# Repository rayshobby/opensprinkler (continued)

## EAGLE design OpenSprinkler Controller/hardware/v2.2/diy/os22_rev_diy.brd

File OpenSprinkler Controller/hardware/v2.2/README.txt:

OpenSprinkler v2.2 (2nd generation)
Changes from 2.1

- Added CH340G USB-serial converter
- ATmega644 now running at 16MHz and preloaded with optiboot bootloader

DIY v2.2_rev and SMT v2.2

- Changed to use MC34063 switching regulator (previously LM2596)
- Added Microchip 24AA02E48 hardware MAC chip

Schematics and Board design files require EagleCAD v6.0 or above.

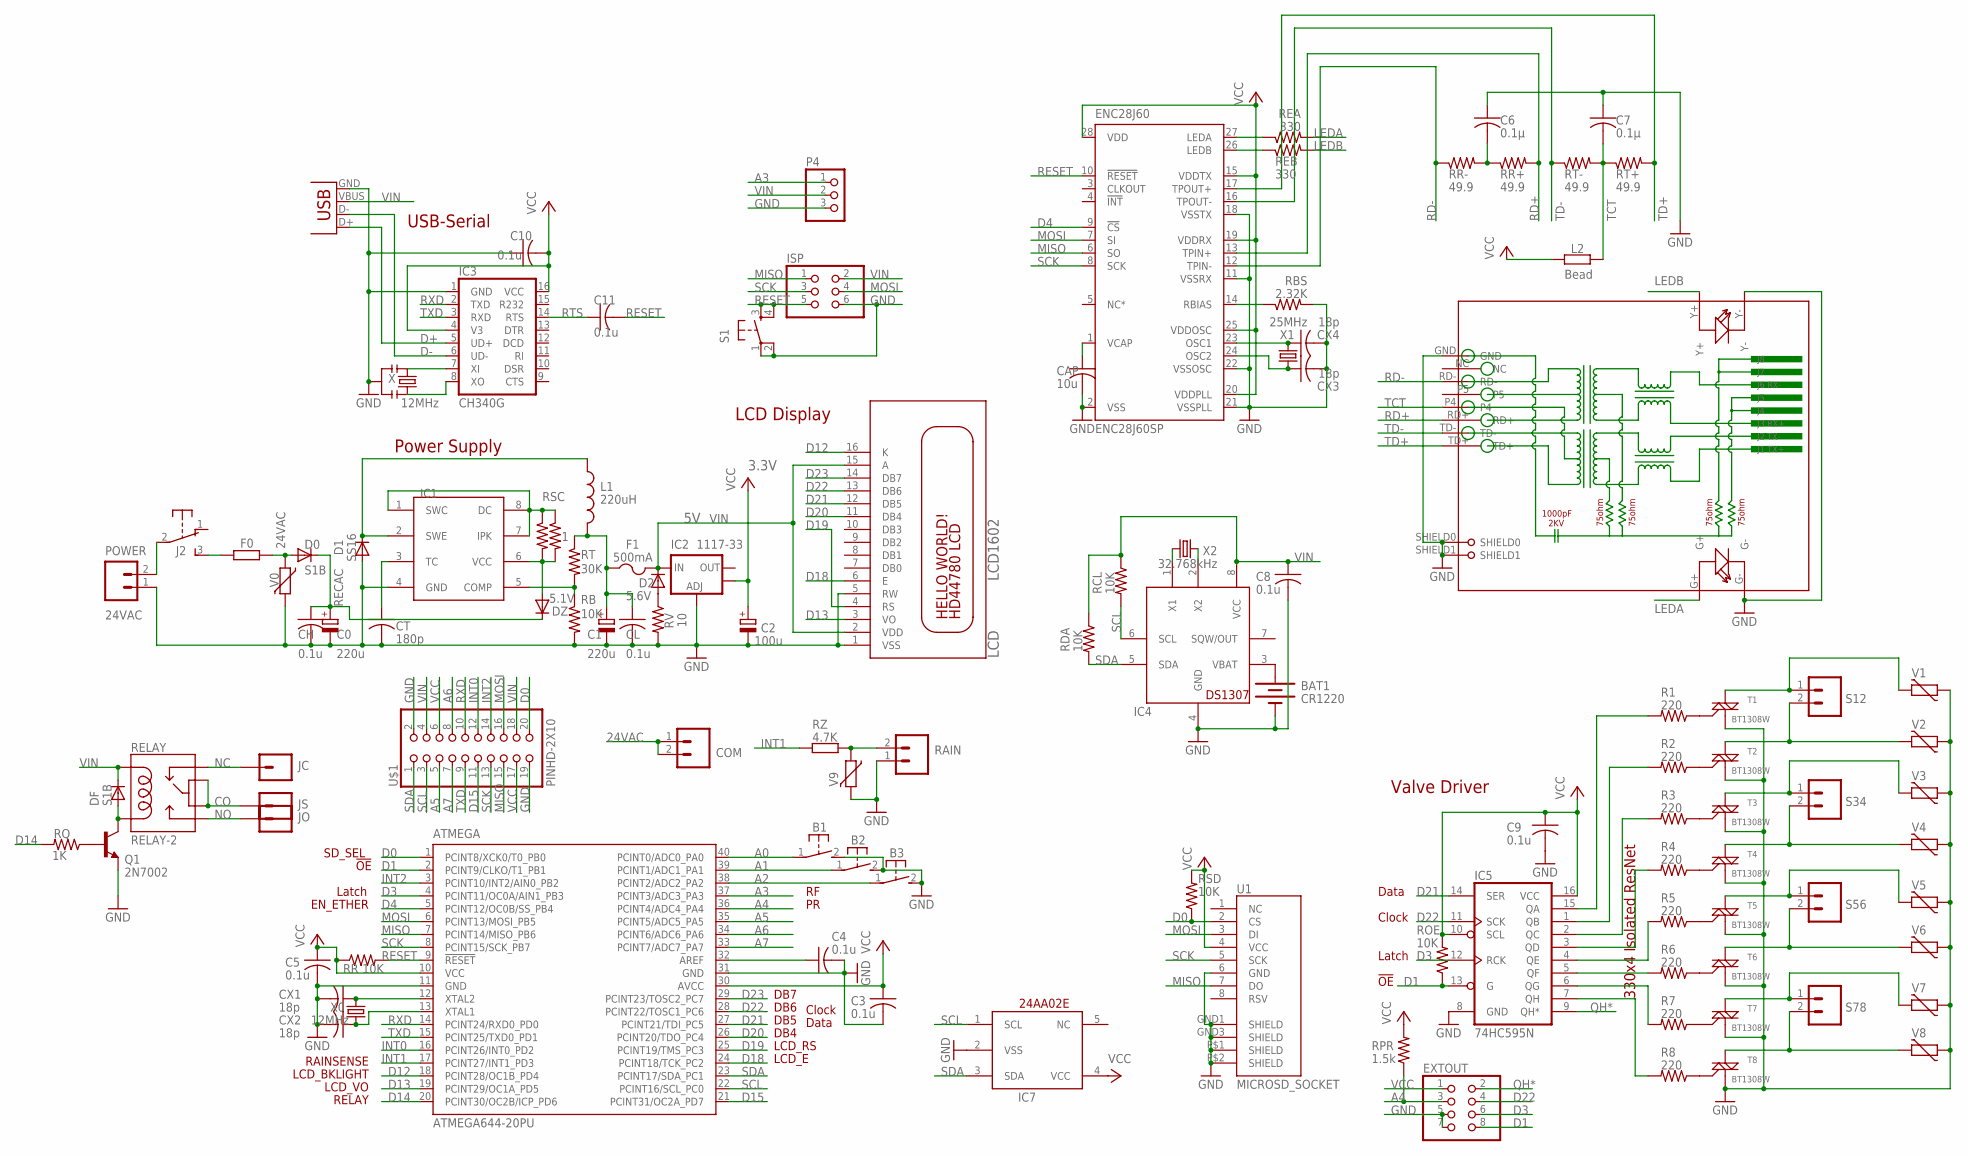
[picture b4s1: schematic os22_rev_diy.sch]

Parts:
ATMEGA: ATMEGA644-20PU; DIL40
B1, B2, B3: 31-XX; B3F-31XX
BAT1: CR1220; BATTCON_12MM_SMT
C0, C1: 220u; E3,5-8
C2: 100u; E2-5
C3, C4, C5, C8, C9, C10, C11: 0.1u; C0603K
C6, C7: 0.1µ; C0603K
CAP: 10u; C0805K
CH: 0.1u; C0603K
CL: 0.1u; C0603K
COM: M025MM-X; SCREWTERMINAL-5MM-2-X
CT: 180p; C0603K
CX1, CX2, CX3, CX4: 18p; C0603K
D0: S1B; DO-214AC
D1: SS16; DO-214AC
D2: 5.6V; MINIMELF
DF: S1B; DO-214AC
DZ: 5.1V; MELF-MLL41
ENC28J60: ENC28J60SP; DIL28-3
EXTOUT: PINHD-2X4; 2X04
F0: R-EU_0411/3V; 0411V
F1: 500mA; 1812
IC1: 34063; SO08
IC2: 1117-33; SOT223
IC3: CH340G; SO16
IC4: DS1307; SO08
IC5: 74HC595N; SO16
IC7: 24AA02E; SOT23-5L
ISP: PINHD-2X3; 2X03
J2: EG1206
JC: M01PTH; 1X01
JO: M01PTH; 1X01
JS: M01PTH; 1X01
L1: 220uH; 0204/5
L2: Bead; R0805
LCD: LCD1602; LCD1602A
P4: PINHD-1X3; 1X03
POWER: 24VAC; SCREWTERMINAL-4MM-2-X
Q1: 2N7002; SOT23-3
R1, R2, R3, R4, R5, R6, R7, R8: 220; R0603
RAIN: M025MM-X; SCREWTERMINAL-5MM-2-X
RB: 10K; R0805
RBS: 2.32K; R0805
RCL: 10K; R0603
RDA: 10K; R0603
REA: 330; R0603
REB: 330; R0603
RELAY: RELAY-2; RELAY-HK4100F
RJ45: HR911105A
ROE: 10K; R0603
RPR: 1.5k; R0603
RQ: 1K; R0603
RR: 10K; R0603
RR+: 49.9; R0805
RR-: 49.9; R0805
RSC, RSC1: 1; R0805
RSD: 10K; R0603
RT: 30K; R0805
RT+: 49.9; R0805
RT-: 49.9; R0805
RV: 10; R0805
RZ: 4.7K; R0805
S1: TAC_SWITCHPTH; TACTILE-PTH
S12, S34, S56, S78: M025MM-X; SCREWTERMINAL-5MM-2-X
T1, T2, T3, T4, T5, T6, T7, T8: BT1308W; TO-92
U1: MICROSD_SOCKET; MICRO-SD-SOCKET-TAOBAO
U$1: PINHD-2X10; 2X10-CLEANBIG
USB: USBPTH; USB-B-PTH
V0, V1, V2, V3, V4, V5, V6, V7, V8, V9: MOV; R-5
X: 12MHz; RESONATOR-SMD
X0: 12MHz; HC49U-V
X1: 25MHz; HC49U-V
X2: 32.768kHz; TC38H

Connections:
24VAC: COM.1, COM.2, D0.A, F0.2, V0.1
A0: ATMEGA.40 (PCINT0/ADC0_PA0), B1.1
A1: ATMEGA.39 (PCINT1/ADC1_PA1), B2.1
A2: ATMEGA.38 (PCINT2/ADC2_PA2), B3.1
A3: ATMEGA.37 (PCINT3/ADC3_PA3), P4.1
A4: ATMEGA.36 (PCINT4/ADC4_PA4), EXTOUT.3, RPR.1
A5: ATMEGA.35 (PCINT5/ADC5_PA5), U$1.5
A6: ATMEGA.34 (PCINT6/ADC6_PA6), U$1.8
A7: ATMEGA.33 (PCINT7/ADC7_PA7), U$1.7
AREF: ATMEGA.32 (AREF), C4.1
CO: JS.1, RELAY.5, RELAY.6
D0: ATMEGA.1 (PCINT8/XCK0/T0_PB0), RSD.1, U1.2 (CS), U$1.20
D1: ATMEGA.2 (PCINT9/CLKO/T1_PB1), EXTOUT.8, IC5.13 (G), ROE.1
D3: ATMEGA.4 (PCINT11/OC0A/AIN1_PB3), EXTOUT.6, IC5.12 (RCK)
D4: ATMEGA.5 (PCINT12/OC0B/SS_PB4), ENC28J60.9 (!CS)
D12: ATMEGA.18 (PCINT28/OC1B_PD4), LCD.16 (K)
D13: ATMEGA.19 (PCINT29/OC1A_PD5), LCD.3 (VO)
D14: ATMEGA.20 (PCINT30/OC2B/ICP_PD6), RQ.2
D15: ATMEGA.21 (PCINT31/OC2A_PD7), U$1.11
D18: ATMEGA.24 (PCINT18/TCK_PC2), LCD.6 (E)
D19: ATMEGA.25 (PCINT19/TMS_PC3), LCD.4 (RS)
D20: ATMEGA.26 (PCINT20/TDO_PC4), LCD.11 (DB4)
D21: ATMEGA.27 (PCINT21/TDI_PC5), IC5.14 (SER), LCD.12 (DB5)
D22: ATMEGA.28 (PCINT22/TOSC1_PC6), EXTOUT.4, IC5.11 (SCK), LCD.13 (DB6)
D23: ATMEGA.29 (PCINT23/TOSC2_PC7), LCD.14 (DB7)
D+: IC3.5 (UD+), USB.D+
D-: IC3.6 (UD-), USB.D-
GND: ATMEGA.11 (GND), ATMEGA.31 (GND), B1.2 (S), B2.2 (S), B3.2 (S), BAT1.P$1 (-), C0.-, C1.-, C2.-, C3.2, C4.2, C5.2, C6.1, C7.1, C8.2, C9.2, C10.1, CAP.2, CH.2, CL.2, CT.2, CX1.2, CX2.2, CX3.2, CX4.2, D1.A, ENC28J60.2 (VSS), ENC28J60.11 (VSSRX), ENC28J60.18 (VSSTX), ENC28J60.21 (VSSPLL), ENC28J60.22 (VSSOSC), EXTOUT.5, EXTOUT.7, IC1.4 (GND), IC2.1 (ADJ), IC3.1 (GND), IC4.4 (GND), IC5.8 (GND), IC7.2 (VSS), ISP.6, LCD.1 (VSS), LCD.5 (RW), P4.3, POWER.1, Q1.2 (E), RAIN.1, RB.2, RBS.2, RJ45.G-, RJ45.GND, RJ45.SHIELD0, RJ45.SHIELD1, RJ45.Y-, RV.2, S1.1, S1.2, T1.1 (M1), T2.1 (M1), T3.1 (M1), T4.1 (M1), T5.1 (M1), T6.1 (M1), T7.1 (M1), T8.1 (M1), U1.6 (GND), U1.GND1 (SHIELD), U1.GND3 (SHIELD), U1.P$1 (SHIELD), U1.P$2 (SHIELD), U$1.2, U$1.19, USB.GND, V0.2, V1.1, V2.1, V3.1, V4.1, V5.1, V6.1, V7.1, V8.1, V9.2, X.2
INT0: ATMEGA.16 (PCINT26/INT0_PD2), U$1.12
INT1: ATMEGA.17 (PCINT27/INT1_PD3), RZ.2
INT2: ATMEGA.3 (PCINT10/INT2/AIN0_PB2), U$1.14
LEDA: REA.2, RJ45.G+
LEDB: REB.2, RJ45.Y+
MISO: ATMEGA.7 (PCINT14/MISO_PB6), ENC28J60.6 (SO), ISP.1, U1.7 (DO), U$1.15
MOSI: ATMEGA.6 (PCINT13/MOSI_PB5), ENC28J60.7 (SI), ISP.4, U1.3 (DI), U$1.16
unnamed: IC4.2 (X2), X2.2
unnamed: IC4.1 (X1), X2.1
unnamed: R1.1, T1.2 (G)
unnamed: IC5.5 (QF), R6.2
unnamed: IC5.6 (QG), R7.2
unnamed: J2.2, POWER.2
unnamed: IC5.7 (QH), R8.2
unnamed: BAT1.P$2 (+), IC4.3 (VBAT)
unnamed: D1.C, IC1.2 (SWE), L1.1
unnamed: IC5.4 (QE), R5.2
unnamed: IC5.3 (QD), R4.2
unnamed: IC5.2 (QC), R3.2
unnamed: IC5.1 (QB), R2.2
unnamed: IC5.15 (QA), R1.2
unnamed: R2.1, T2.2 (G)
unnamed: S12.1, T1.3 (M2), V1.2
unnamed: S12.2, T2.3 (M2), V2.2
unnamed: S34.1, T3.3 (M2), V3.2
unnamed: ENC28J60.14 (RBIAS), RBS.1
unnamed: S34.2, T4.3 (M2), V4.2
unnamed: R3.1, T3.2 (G)
unnamed: S56.1, T5.3 (M2), V5.2
unnamed: S56.2, T6.3 (M2), V6.2
unnamed: S78.1, T7.3 (M2), V7.2
unnamed: S78.2, T8.3 (M2), V8.2
unnamed: R4.1, T4.2 (G)
unnamed: R5.1, T5.2 (G)
unnamed: R6.1, T6.2 (G)
unnamed: R7.1, T7.2 (G)
unnamed: RAIN.2, RZ.1, V9.1
unnamed: F0.1, J2.3 (S)
unnamed: CAP.1, ENC28J60.1 (VCAP)
unnamed: ENC28J60.27 (LEDA), REA.1
unnamed: DF.A, Q1.3 (C), RELAY.9
unnamed: ENC28J60.26 (LEDB), REB.1
unnamed: DZ.A, IC1.6 (VCC), RSC.2, RSC1.2
unnamed: D2.A, RV.1
unnamed: Q1.1 (B), RQ.1
unnamed: CX3.1, ENC28J60.24 (OSC2), X1.2
unnamed: CX4.1, ENC28J60.23 (OSC1), X1.1
unnamed: R8.1, T8.2 (G)
unnamed: IC3.7 (XI), X.1
unnamed: IC1.1 (SWC), IC1.7 (IPK), IC1.8 (DC), RSC.1, RSC1.1
unnamed: ATMEGA.12 (XTAL2), CX1.1, X0.2
unnamed: ATMEGA.13 (XTAL1), CX2.1, X0.1
unnamed: IC3.8 (XO), X.3
unnamed: CT.1, IC1.3 (TC)
unnamed: C6.2, RR+.1, RR-.2
unnamed: IC1.5 (COMP), RB.1, RT.2
NC: JC.1, RELAY.1
NO: JO.1, RELAY.10
QH*: EXTOUT.2, IC5.9 (QH*)
RD+: ENC28J60.13 (TPIN+), RJ45.RD+, RR+.2
RD-: ENC28J60.12 (TPIN-), RJ45.RD-, RR-.1
RECAC: C0.+, CH.1, D0.C, DZ.C
RESET: ATMEGA.9 (!RESET), C11.2, ENC28J60.10 (!RESET), ISP.5, RR.2, S1.3, S1.4
RTS: C11.1, IC3.14 (RTS)
RXD: ATMEGA.14 (PCINT24/RXD0_PD0), IC3.2 (TXD), U$1.10
SCK: ATMEGA.8 (PCINT15/SCK_PB7), ENC28J60.8 (SCK), ISP.3, U1.5 (SCK), U$1.13
SCL: ATMEGA.22 (PCINT16/SCL_PC0), IC4.6 (SCL), IC7.1 (SCL), RCL.2, U$1.3
SDA: ATMEGA.23 (PCINT17/SDA_PC1), IC4.5 (SDA), IC7.3 (SDA), RDA.2, U$1.1
TCT: C7.2, L2.1, RJ45.P4, RT+.1, RT-.2
TD+: ENC28J60.17 (TPOUT+), RJ45.TD+, RT+.2
TD-: ENC28J60.16 (TPOUT-), RJ45.TD-, RT-.1
TXD: ATMEGA.15 (PCINT25/TXD0_PD1), IC3.3 (RXD), U$1.9
VCC: ATMEGA.10 (VCC), ATMEGA.30 (AVCC), C2.+, C3.1, C5.1, C9.1, C10.2, ENC28J60.15 (VDDTX), ENC28J60.19 (VDDRX), ENC28J60.20 (VDDPLL), ENC28J60.25 (VDDOSC), ENC28J60.28 (VDD), EXTOUT.1, IC2.4 (OUT), IC3.4 (V3), IC3.16 (VCC), IC5.10 (SCL), IC5.16 (VCC), IC7.4 (VCC), L2.2, ROE.2, RPR.2, RR.1, RSD.2, U1.4 (VCC), U$1.6, U$1.17
VIN: C8.1, D2.C, DF.C, F1.2, IC2.3 (IN), IC4.8 (VCC), ISP.2, LCD.2 (VDD), LCD.15 (A), P4.2, RCL.1, RDA.1, RELAY.2, U$1.4, U$1.18, USB.VBUS
VIN1: C1.+, CL.1, F1.1, L1.2, RT.1

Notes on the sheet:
Valve Driver
Data
Clock
Latch
DB4
330x4 Isolated ResNet
LCD Display
EN_ETHER
3.3V
DB7
LCD_E
LCD_RS
DB6
DB5
!OE
RAINSENSE
LCD_BKLIGHT
LCD_VO
SD_SEL
RELAY
USB-Serial
Power Supply

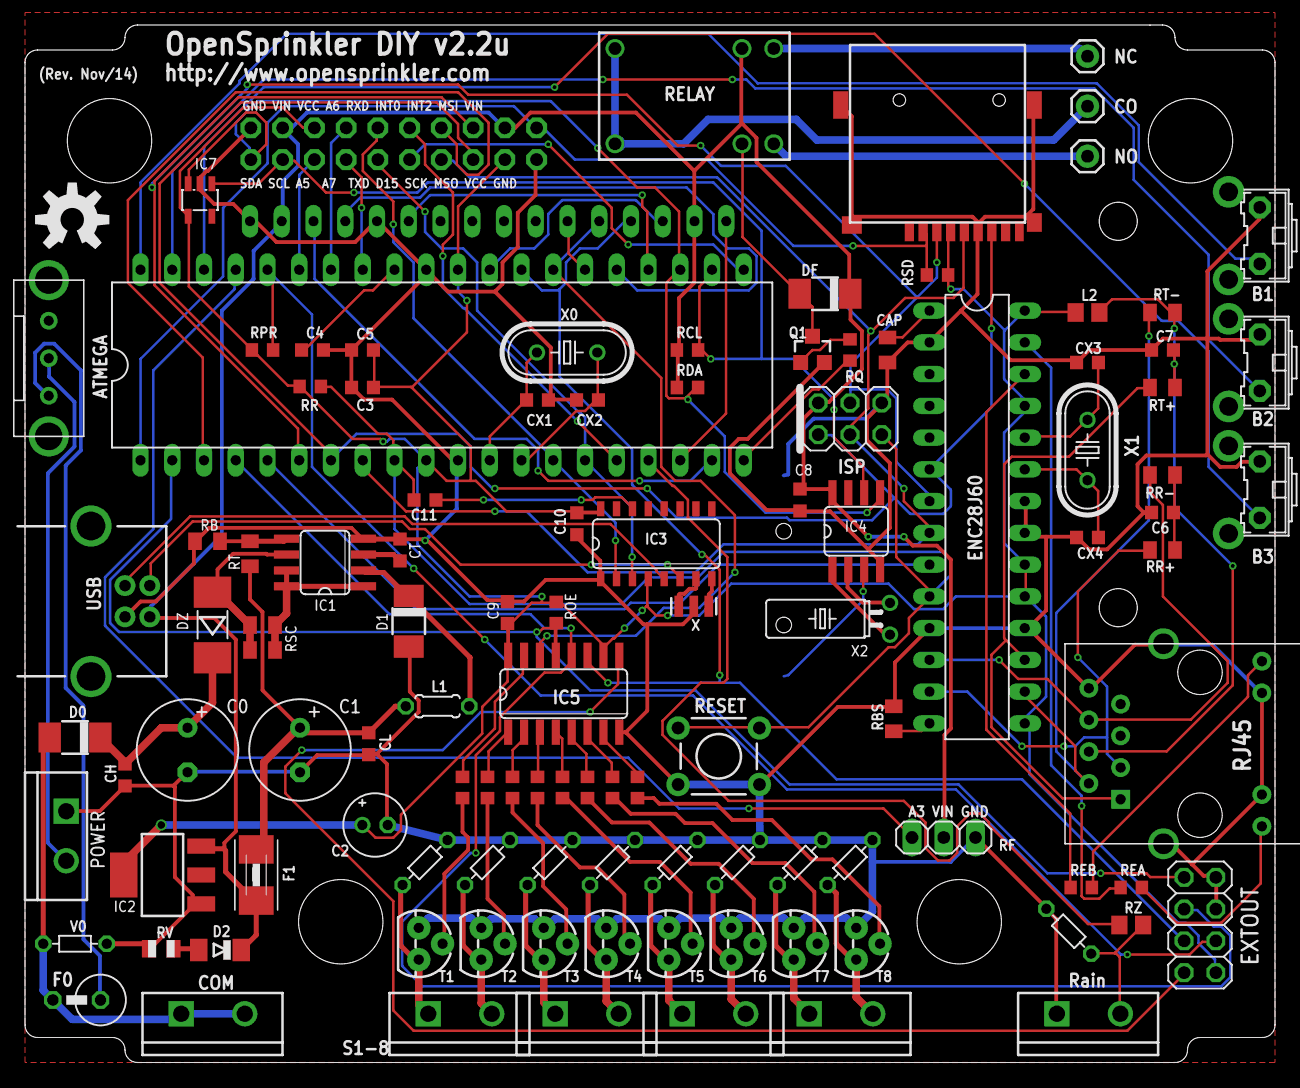
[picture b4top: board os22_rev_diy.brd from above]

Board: 2 copper layers, 100.0 x 83.0 mm, 113 parts (1 on the bottom side), 103 nets.

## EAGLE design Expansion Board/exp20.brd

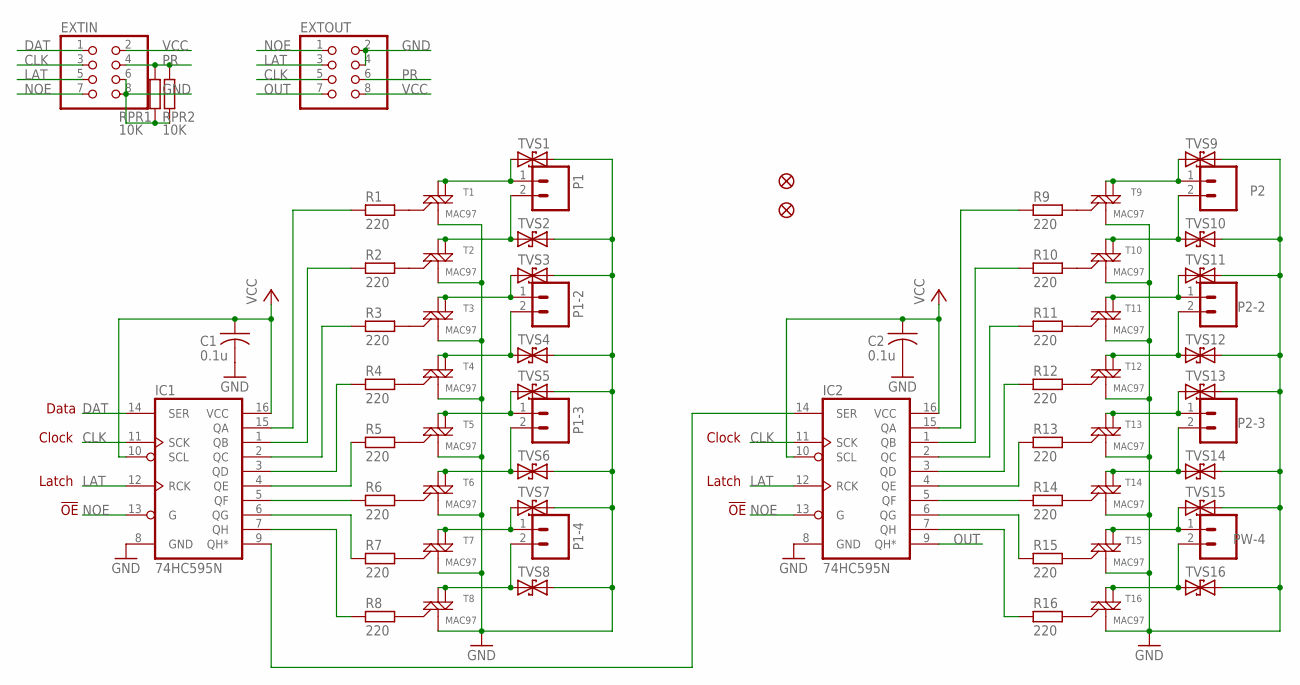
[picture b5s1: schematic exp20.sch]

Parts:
C1, C2: 0.1u; C0805K
EXTIN: PINHD-2X4/90; 2X04/90
EXTOUT: PINHD-2X4/90; 2X04/90
IC1, IC2: 74HC595N; SO16
JP1, JP2: FIDUCIAL1X2; FIDUCIAL-1X2
P1, P1-2, P1-3, P1-4, P2, P2-2, P2-3: M025MM-X; SCREWTERMINAL-5MM-2-X
PW-4: M025MM-X; SCREWTERMINAL-5MM-2-X
R1, R2, R3, R4, R5, R6, R7, R8, R9, R10, R11, R12, R13, R14, R15, R16: 220; R0805
RPR1, RPR2: 10K; R0805
T1, T2, T3, T4, T5, T6, T7, T8, T9, T10, T11, T12, T13, T14, T15, T16: MAC97; SOT223
TVS1, TVS2, TVS3, TVS4, TVS5, TVS6, TVS7, TVS8, TVS9, TVS10, TVS11, TVS12, TVS13, TVS14, TVS15, TVS16: TVSSMB; SMB

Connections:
CLK: EXTIN.3, EXTOUT.5, IC1.11 (SCK), IC2.11 (SCK)
DAT: EXTIN.1, IC1.14 (SER)
GND: C1.2, C2.2, EXTIN.6, EXTIN.8, EXTOUT.2, EXTOUT.4, IC1.8 (GND), IC2.8 (GND), RPR1.1, RPR2.1, T1.1 (M1), T2.1 (M1), T3.1 (M1), T4.1 (M1), T5.1 (M1), T6.1 (M1), T7.1 (M1), T8.1 (M1), T9.1 (M1), T10.1 (M1), T11.1 (M1), T12.1 (M1), T13.1 (M1), T14.1 (M1), T15.1 (M1), T16.1 (M1), TVS1.C (2), TVS2.C (2), TVS3.C (2), TVS4.C (2), TVS5.C (2), TVS6.C (2), TVS7.C (2), TVS8.C (2), TVS9.C (2), TVS10.C (2), TVS11.C (2), TVS12.C (2), TVS13.C (2), TVS14.C (2), TVS15.C (2), TVS16.C (2)
LAT: EXTIN.5, EXTOUT.3, IC1.12 (RCK), IC2.12 (RCK)
unnamed: P1.1, T1.2 (M2), T1.4 (M2-4), TVS1.A (1)
unnamed: P1-2.1, T3.2 (M2), T3.4 (M2-4), TVS3.A (1)
unnamed: P1-3.1, T5.2 (M2), T5.4 (M2-4), TVS5.A (1)
unnamed: IC1.5 (QF), R6.2
unnamed: IC1.6 (QG), R7.2
unnamed: P1-4.1, T7.2 (M2), T7.4 (M2-4), TVS7.A (1)
unnamed: IC1.7 (QH), R8.2
unnamed: R1.1, T1.3 (G)
unnamed: R2.1, T2.3 (G)
unnamed: IC1.4 (QE), R5.2
unnamed: IC1.3 (QD), R4.2
unnamed: IC1.2 (QC), R3.2
unnamed: IC1.1 (QB), R2.2
unnamed: IC1.15 (QA), R1.2
unnamed: R3.1, T3.3 (G)
unnamed: R4.1, T4.3 (G)
unnamed: P1.2, T2.2 (M2), T2.4 (M2-4), TVS2.A (1)
unnamed: R5.1, T5.3 (G)
unnamed: R6.1, T6.3 (G)
unnamed: P1-2.2, T4.2 (M2), T4.4 (M2-4), TVS4.A (1)
unnamed: R7.1, T7.3 (G)
unnamed: R8.1, T8.3 (G)
unnamed: P1-3.2, T6.2 (M2), T6.4 (M2-4), TVS6.A (1)
unnamed: IC2.5 (QF), R14.2
unnamed: P1-4.2, T8.2 (M2), T8.4 (M2-4), TVS8.A (1)
unnamed: IC2.6 (QG), R15.2
unnamed: IC2.7 (QH), R16.2
unnamed: IC2.4 (QE), R13.2
unnamed: IC2.3 (QD), R12.2
unnamed: IC2.2 (QC), R11.2
unnamed: IC2.1 (QB), R10.2
unnamed: IC2.15 (QA), R9.2
unnamed: P2.2, T10.2 (M2), T10.4 (M2-4), TVS10.A (1)
unnamed: P2-2.2, T12.2 (M2), T12.4 (M2-4), TVS12.A (1)
unnamed: P2-3.2, T14.2 (M2), T14.4 (M2-4), TVS14.A (1)
unnamed: PW-4.2, T16.2 (M2), T16.4 (M2-4), TVS16.A (1)
unnamed: P2.1, T9.2 (M2), T9.4 (M2-4), TVS9.A (1)
unnamed: P2-2.1, T11.2 (M2), T11.4 (M2-4), TVS11.A (1)
unnamed: P2-3.1, T13.2 (M2), T13.4 (M2-4), TVS13.A (1)
unnamed: PW-4.1, T15.2 (M2), T15.4 (M2-4), TVS15.A (1)
unnamed: R9.1, T9.3 (G)
unnamed: R10.1, T10.3 (G)
unnamed: R11.1, T11.3 (G)
unnamed: R12.1, T12.3 (G)
unnamed: R13.1, T13.3 (G)
unnamed: R14.1, T14.3 (G)
unnamed: R15.1, T15.3 (G)
unnamed: R16.1, T16.3 (G)
unnamed: IC1.9 (QH*), IC2.14 (SER)
NOE: EXTIN.7, EXTOUT.1, IC1.13 (G), IC2.13 (G)
OUT: EXTOUT.7, IC2.9 (QH*)
PR: EXTIN.4, EXTOUT.6, RPR1.2, RPR2.2
VCC: C1.1, C2.1, EXTIN.2, EXTOUT.8, IC1.10 (SCL), IC1.16 (VCC), IC2.10 (SCL), IC2.16 (VCC)

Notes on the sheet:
Data
Clock
Latch
!OE

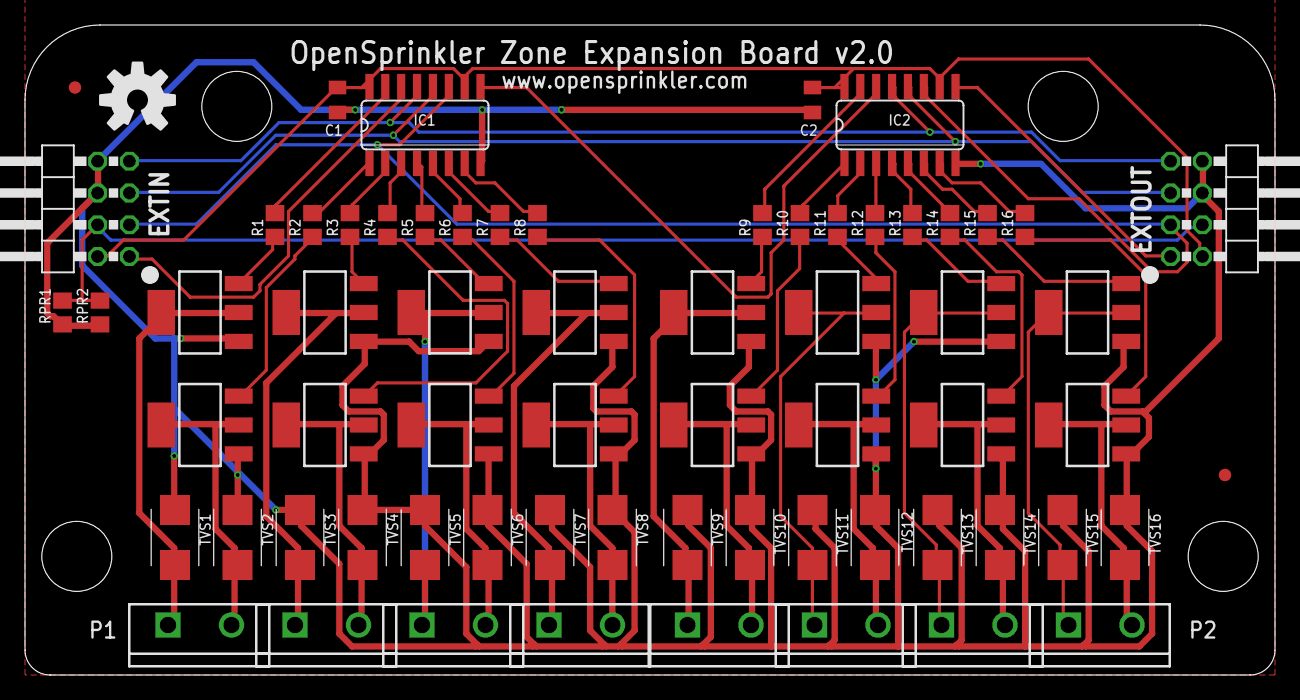
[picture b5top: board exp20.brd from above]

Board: 2 copper layers, 100.0 x 52.0 mm, 66 parts (0 on the bottom side), 57 nets.

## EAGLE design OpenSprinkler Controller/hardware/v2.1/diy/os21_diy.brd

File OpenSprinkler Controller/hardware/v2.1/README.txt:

OpenSprinkler v2.1 (2nd generation)
Changes from 2.0

- Removed ATtiny45 (used to serve as USBtinyISP programmer).
- ATmega644 now running at 12MHz and preloaded with USBasp bootloader.
- Added per-station TVS (smt version) / MOV (diy version).
- Added 120V/2A mini-relay (connected to pin D14.
- Added 2A fuse on the 24V AC line.
- 24V AC terminal block changed to orange colored 3.96mm spacing.

Schematics and Board design files require EagleCAD v6.0 or above.

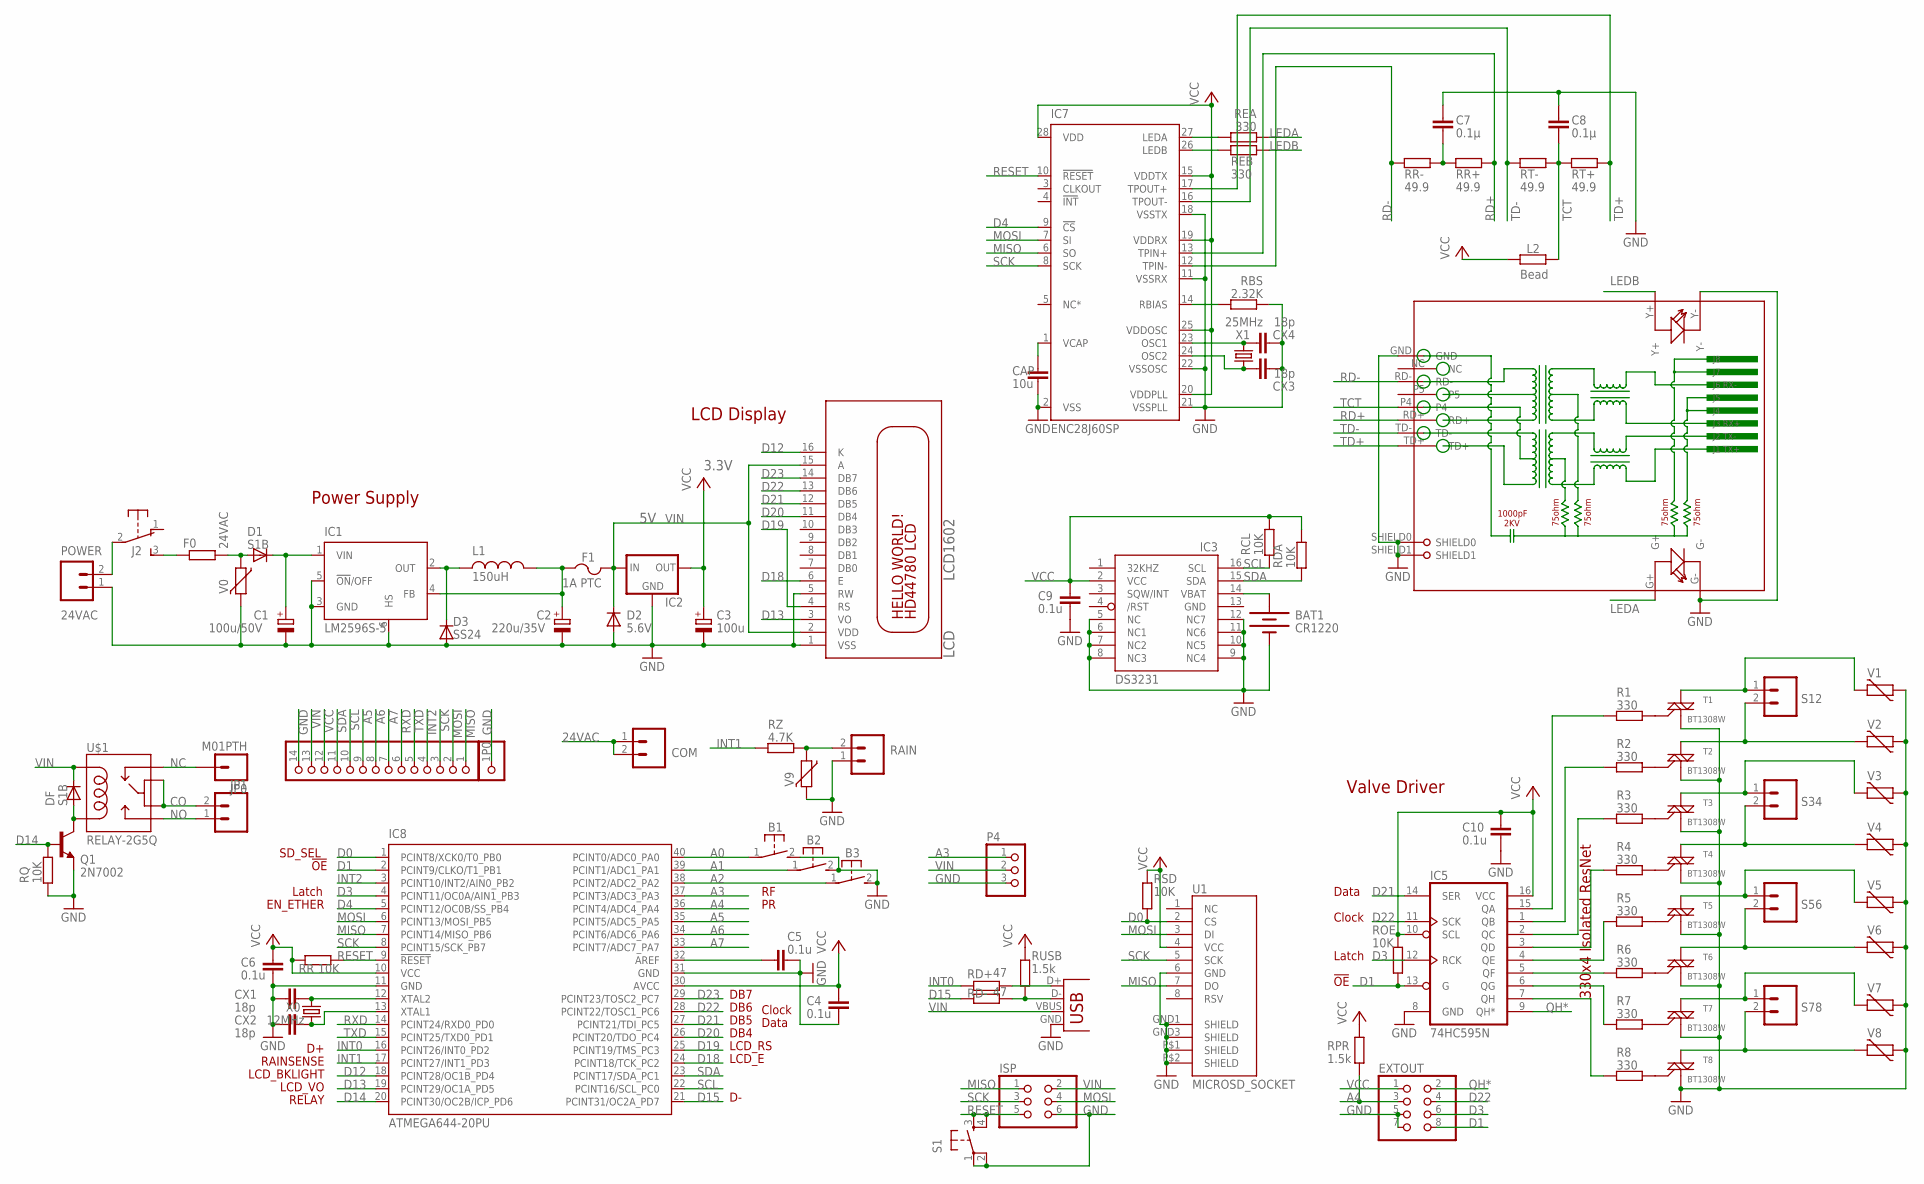
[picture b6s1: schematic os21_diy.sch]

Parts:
B1, B2, B3: 31-XX; B3F-31XX
BAT1: CR1220; BATTCON_12MM_SMT
C1: 100u/50V; E3,5-8
C2: 220u/35V; E3,5-8
C3: 100u; E2-5
C4, C5, C6, C9, C10: 0.1u; C0805
C7, C8: 0.1µ; C0805
CAP: 10u; C0805
COM: M025MM-X; SCREWTERMINAL-5MM-2-X
CX1, CX2, CX3, CX4: 18p; C0805
D1: S1B; DO-214AC
D2: 5.6V; MINIMELF
D3: SS24; DO-214AC
DF: S1B; DO-214AC
EXTOUT: PINHD-2X4; 2X04
F0: R-EU_0411/3V; 0411V
F1: 1A PTC; 1812
IC1: LM2596S-5; TO263-5
IC2: MCP1700SOT233; SOT23
IC3: DS3231/SO; SO16W
IC5: 74HC595N; SO16
IC7: ENC28J60SP; DIL28-3
IC8: ATMEGA644-20PU; DIL40
ISP: PINHD-2X3; 2X03
J2: EG1206
JP0: M01PTH; 1X01
JP1: M025MM-X; SCREWTERMINAL-5MM-2-X
L1: 150uH; CDRH125
L2: Bead; R0805
LCD: LCD1602; LCD1602A
P0: PINHD-1X14-CB; 1X14-CB
P1: PINHD-1X1CB; 1X01-CLEANBIG
P4: PINHD-1X3; 1X03
POWER: 24VAC; SCREWTERMINAL-4MM-2-X
Q1: 2N7002; SOT23-3
R1, R2, R3, R4, R5, R6, R7, R8: 330; R0805
RAIN: M025MM-X; SCREWTERMINAL-5MM-2-X
RBS: 2.32K; R0805
RCL: 10K; R0805
RD+: 47; R0805
RD-: 47; R0805
RDA: 10K; R0805
REA: 330; R0805
REB: 330; R0805
RJ45: HR911105A
ROE: 10K; R0805
RPR: 1.5k; R0805
RQ: 10K; R0805
RR: 10K; R0805
RR+: 49.9; R0805
RR-: 49.9; R0805
RSD: 10K; R0805
RT+: 49.9; R0805
RT-: 49.9; R0805
RUSB: 1.5k; R0805
RZ: 4.7K; R0805
S1: TAC_SWITCHSMD; TACTILE_SWITCH_SMD
S12, S34, S56, S78: M025MM-X; SCREWTERMINAL-5MM-2-X
T1, T2, T3, T4, T5, T6, T7, T8: BT1308W; TO-92
U1: MICROSD_SOCKET; MICRO-SD-SOCKET-TAOBAO
U$1: RELAY-2G5Q; RELAY-G5V
USB: USBPTH; USB-B-PTH
V0, V1, V2, V3, V4, V5, V6, V7, V8, V9: MOV; R-5
X0: 12MHz; HC49U-V
X1: 25MHz; HC49U-V

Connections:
24VAC: COM.1, COM.2, D1.A, F0.2, V0.1
A0: B1.1, IC8.40 (PCINT0/ADC0_PA0)
A1: B2.1, IC8.39 (PCINT1/ADC1_PA1)
A2: B3.1, IC8.38 (PCINT2/ADC2_PA2)
A3: IC8.37 (PCINT3/ADC3_PA3), P4.1
A4: EXTOUT.3, IC8.36 (PCINT4/ADC4_PA4), RPR.1
A5: IC8.35 (PCINT5/ADC5_PA5), P0.9
A6: IC8.34 (PCINT6/ADC6_PA6), P0.8
A7: IC8.33 (PCINT7/ADC7_PA7), P0.7
AREF: C5.1, IC8.32 (AREF)
CO: JP1.2, U$1.5, U$1.6
D0: IC8.1 (PCINT8/XCK0/T0_PB0), RSD.1, U1.2 (CS)
D1: EXTOUT.8, IC5.13 (G), IC8.2 (PCINT9/CLKO/T1_PB1), ROE.1
D3: EXTOUT.6, IC5.12 (RCK), IC8.4 (PCINT11/OC0A/AIN1_PB3)
D4: IC7.9 (!CS), IC8.5 (PCINT12/OC0B/SS_PB4)
D12: IC8.18 (PCINT28/OC1B_PD4), LCD.16 (K)
D13: IC8.19 (PCINT29/OC1A_PD5), LCD.3 (VO)
D14: IC8.20 (PCINT30/OC2B/ICP_PD6), Q1.1 (B), RQ.1
D15: IC8.21 (PCINT31/OC2A_PD7), RD-.1
D18: IC8.24 (PCINT18/TCK_PC2), LCD.6 (E)
D19: IC8.25 (PCINT19/TMS_PC3), LCD.4 (RS)
D20: IC8.26 (PCINT20/TDO_PC4), LCD.11 (DB4)
D21: IC5.14 (SER), IC8.27 (PCINT21/TDI_PC5), LCD.12 (DB5)
D22: EXTOUT.4, IC5.11 (SCK), IC8.28 (PCINT22/TOSC1_PC6), LCD.13 (DB6)
D23: IC8.29 (PCINT23/TOSC2_PC7), LCD.14 (DB7)
GND: B1.2 (S), B2.2 (S), B3.2 (S), BAT1.P$1 (-), C1.-, C2.-, C3.-, C4.2, C5.2, C6.2, C7.1, C8.1, C9.2, C10.2, CAP.2, CX1.2, CX2.2, CX3.2, CX4.2, D2.A, D3.A, EXTOUT.5, EXTOUT.7, IC1.3 (GND), IC1.5 (!ON!/OFF), IC1.6 (HS), IC2.1 (GND), IC3.5 (NC), IC3.6 (NC1), IC3.7 (NC2), IC3.8 (NC3), IC3.9 (NC4), IC3.10 (NC5), IC3.11 (NC6), IC3.12 (NC7), IC3.13 (GND), IC5.8 (GND), IC7.2 (VSS), IC7.11 (VSSRX), IC7.18 (VSSTX), IC7.21 (VSSPLL), IC7.22 (VSSOSC), IC8.11 (GND), IC8.31 (GND), ISP.6, LCD.1 (VSS), LCD.5 (RW), P0.14, P1.1, P4.3, POWER.1, Q1.2 (E), RAIN.1, RBS.2, RJ45.G-, RJ45.GND, RJ45.SHIELD0, RJ45.SHIELD1, RJ45.Y-, RQ.2, S1.1, S1.2, T1.1 (M1), T2.1 (M1), T3.1 (M1), T4.1 (M1), T5.1 (M1), T6.1 (M1), T7.1 (M1), T8.1 (M1), U1.6 (GND), U1.GND1 (SHIELD), U1.GND3 (SHIELD), U1.P$1 (SHIELD), U1.P$2 (SHIELD), USB.GND, V0.2, V1.1, V2.1, V3.1, V4.1, V5.1, V6.1, V7.1, V8.1, V9.2
INT0: IC8.16 (PCINT26/INT0_PD2), RD+.1
INT1: IC8.17 (PCINT27/INT1_PD3), RZ.2
INT2: IC8.3 (PCINT10/INT2/AIN0_PB2), P0.4
LEDA: REA.2, RJ45.G+
LEDB: REB.2, RJ45.Y+
MISO: IC7.6 (SO), IC8.7 (PCINT14/MISO_PB6), ISP.1, P0.1, U1.7 (DO)
MOSI: IC7.7 (SI), IC8.6 (PCINT13/MOSI_PB5), ISP.4, P0.2, U1.3 (DI)
unnamed: C1.+, D1.C, IC1.1 (VIN)
unnamed: C2.+, F1.1, IC1.4 (FB), L1.2
unnamed: R1.1, T1.2 (G)
unnamed: IC5.5 (QF), R6.2
unnamed: IC5.6 (QG), R7.2
unnamed: J2.2, POWER.2
unnamed: IC5.7 (QH), R8.2
unnamed: BAT1.P$2 (+), IC3.14 (VBAT)
unnamed: D3.C, IC1.2 (OUT), L1.1
unnamed: IC5.4 (QE), R5.2
unnamed: IC5.3 (QD), R4.2
unnamed: IC5.2 (QC), R3.2
unnamed: IC5.1 (QB), R2.2
unnamed: IC5.15 (QA), R1.2
unnamed: R2.1, T2.2 (G)
unnamed: S12.1, T1.3 (M2), V1.2
unnamed: S12.2, T2.3 (M2), V2.2
unnamed: S34.1, T3.3 (M2), V3.2
unnamed: IC7.14 (RBIAS), RBS.1
unnamed: S34.2, T4.3 (M2), V4.2
unnamed: R3.1, T3.2 (G)
unnamed: S56.1, T5.3 (M2), V5.2
unnamed: S56.2, T6.3 (M2), V6.2
unnamed: S78.1, T7.3 (M2), V7.2
unnamed: S78.2, T8.3 (M2), V8.2
unnamed: R4.1, T4.2 (G)
unnamed: R5.1, T5.2 (G)
unnamed: R6.1, T6.2 (G)
unnamed: R7.1, T7.2 (G)
unnamed: RAIN.2, RZ.1, V9.1
unnamed: F0.1, J2.3 (S)
unnamed: CAP.1, IC7.1 (VCAP)
unnamed: IC7.27 (LEDA), REA.1
unnamed: DF.A, Q1.3 (C), U$1.9
unnamed: IC7.26 (LEDB), REB.1
unnamed: RD+.2, USB.D+
unnamed: CX3.1, IC7.24 (OSC2), X1.2
unnamed: CX4.1, IC7.23 (OSC1), X1.1
unnamed: R8.1, T8.2 (G)
unnamed: RD-.2, RUSB.1, USB.D-
unnamed: CX1.1, IC8.12 (XTAL2), X0.2
unnamed: CX2.1, IC8.13 (XTAL1), X0.1
unnamed: C7.2, RR+.1, RR-.2
NC: JP0.1, U$1.1
NO: JP1.1, U$1.10
QH*: EXTOUT.2, IC5.9 (QH*)
RD+: IC7.13 (TPIN+), RJ45.RD+, RR+.2
RD-: IC7.12 (TPIN-), RJ45.RD-, RR-.1
RESET: IC7.10 (!RESET), IC8.9 (!RESET), ISP.5, RR.2, S1.3, S1.4
RXD: IC8.14 (PCINT24/RXD0_PD0), P0.6
SCK: IC7.8 (SCK), IC8.8 (PCINT15/SCK_PB7), ISP.3, P0.3, U1.5 (SCK)
SCL: IC3.16 (SCL), IC8.22 (PCINT16/SCL_PC0), P0.10, RCL.2
SDA: IC3.15 (SDA), IC8.23 (PCINT17/SDA_PC1), P0.11, RDA.2
TCT: C8.2, L2.1, RJ45.P4, RT+.1, RT-.2
TD+: IC7.17 (TPOUT+), RJ45.TD+, RT+.2
TD-: IC7.16 (TPOUT-), RJ45.TD-, RT-.1
TXD: IC8.15 (PCINT25/TXD0_PD1), P0.5
VCC: C3.+, C4.1, C6.1, C9.1, C10.1, EXTOUT.1, IC2.2 (OUT), IC3.2 (VCC), IC5.10 (SCL), IC5.16 (VCC), IC7.15 (VDDTX), IC7.19 (VDDRX), IC7.20 (VDDPLL), IC7.25 (VDDOSC), IC7.28 (VDD), IC8.10 (VCC), IC8.30 (AVCC), L2.2, P0.12, RCL.1, RDA.1, ROE.2, RPR.2, RR.1, RSD.2, RUSB.2, U1.4 (VCC)
VIN: D2.C, DF.C, F1.2, IC2.3 (IN), ISP.2, LCD.2 (VDD), LCD.15 (A), P0.13, P4.2, U$1.2, USB.VBUS

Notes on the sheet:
Power Supply
Valve Driver
Data
Clock
Latch
DB4
330x4 Isolated ResNet
LCD Display
EN_ETHER
3.3V
DB7
LCD_E
LCD_RS
DB6
DB5
!OE
RAINSENSE
LCD_BKLIGHT
LCD_VO
SD_SEL
RELAY

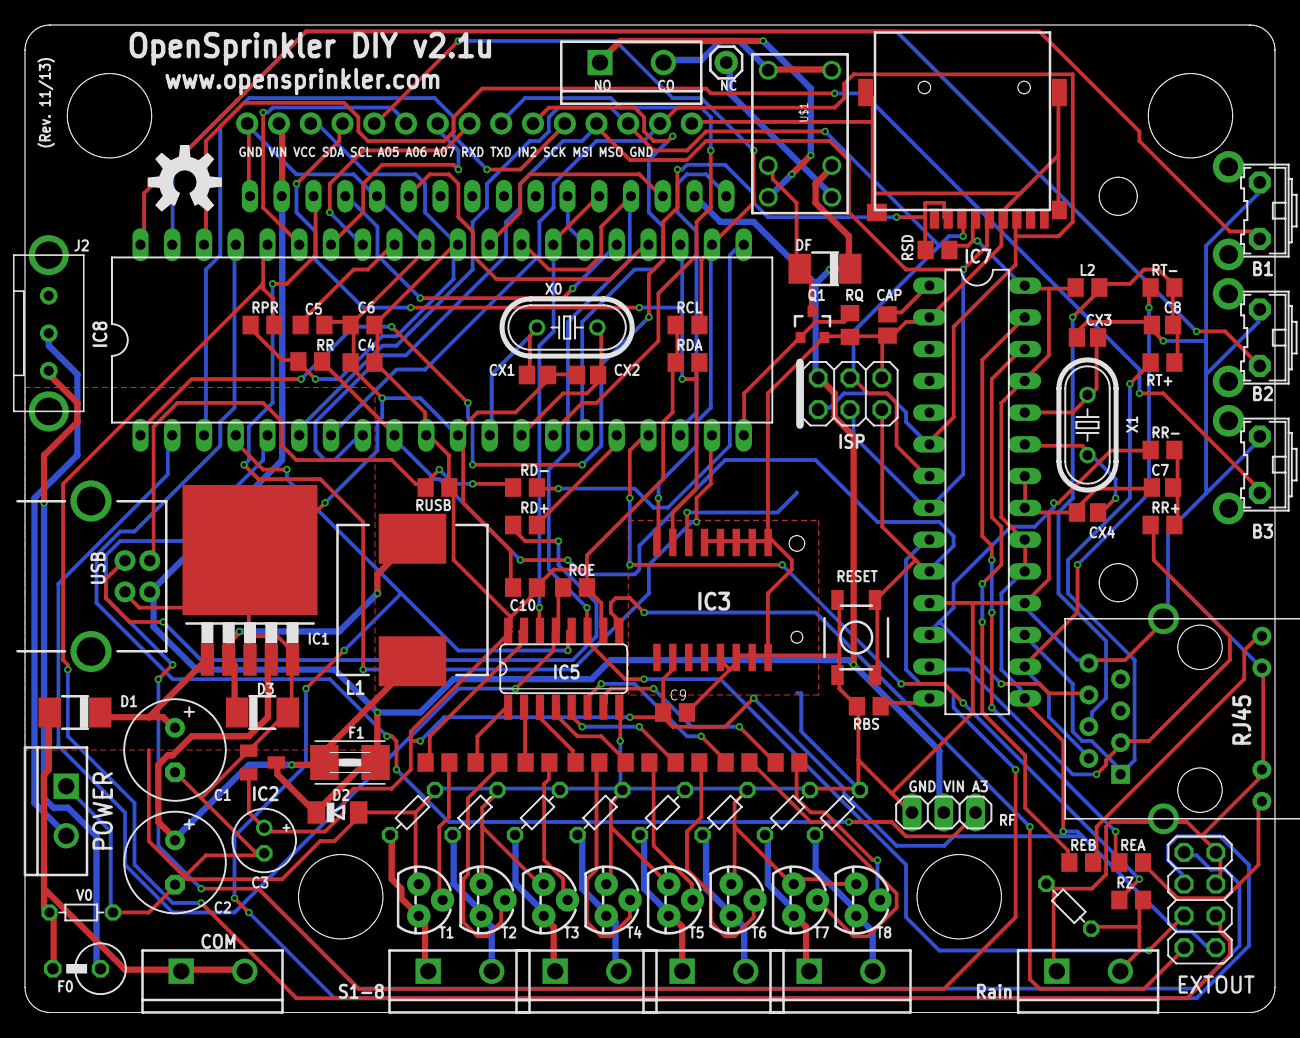
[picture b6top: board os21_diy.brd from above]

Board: 2 copper layers, 100.0 x 79.0 mm, 101 parts (1 on the bottom side), 92 nets.

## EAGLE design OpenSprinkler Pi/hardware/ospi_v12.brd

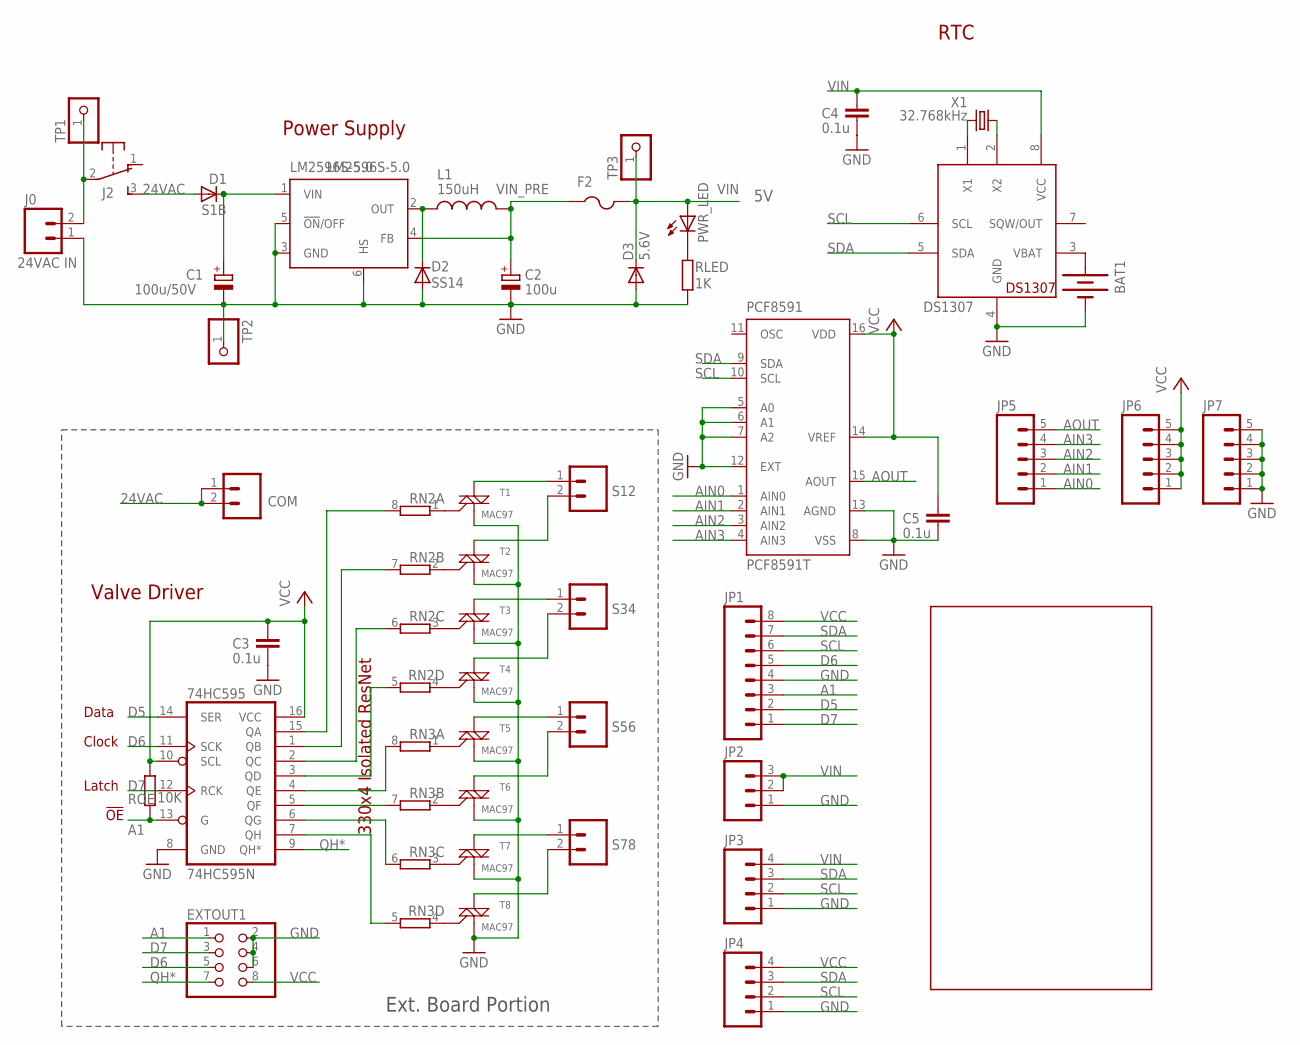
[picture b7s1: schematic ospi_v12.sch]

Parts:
74HC595: 74HC595N; SO16
BAT1: BATTERYBATTERY_12MM_SMT; BATTCON_12MM_SMT
C1: 100u/50V; PANASONIC_E
C2: 100u; PANASONIC_E
C3, C4, C5: 0.1u; C0805
COM: M025MM; SCREWTERMINAL-5MM-2
D1: S1B; DO-214AC
D2: SS14; DO-214AC
D3: 5.6V; MINIMELF
DS1307: DS1307; SO08
EXTOUT1: PINHD-2X4/90; 2X04/90
F2: PTCFUSE-1812; 1812
J0: 24VAC IN; SCREWTERMINAL-5MM-2
J2: EG1206
JP1: M08LOCK; 1X08_LOCK
JP2: M03LOCK; 1X03_LOCK
JP3, JP4: M04LOCK; 1X04_LOCK
JP5, JP6, JP7: M05LOCK; 1X05_LOCK
L1: 150uH; CDRH125
LM2596S-5.0: LM2596S-5.0; TO263-5
PCF8591: PCF8591T; SO16W
PWR_LED: LEDCHIPLED_0805; CHIPLED_0805
RLED: 1K; R0805
RN2, RN3: 4R-NEXB38V; EXB38V
ROE: 10K; R0805
S12, S34, S56, S78: M025MM; SCREWTERMINAL-5MM-2
T1, T2, T3, T4, T5, T6, T7, T8: MAC97; SOT223
TP1, TP2, TP3: PINHD-1X1CB; 1X01-CLEANBIG
U$2: OSPI
X1: 32.768kHz; MM20SS

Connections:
24VAC: COM.1, COM.2, D1.A, J2.3 (S)
A1: 74HC595.13 (G), EXTOUT1.1, JP1.3, ROE.1
AIN0: JP5.1, PCF8591.1 (AIN0)
AIN1: JP5.2, PCF8591.2 (AIN1)
AIN2: JP5.3, PCF8591.3 (AIN2)
AIN3: JP5.4, PCF8591.4 (AIN3)
AOUT: JP5.5, PCF8591.15 (AOUT)
D5: 74HC595.14 (SER), JP1.2
D6: 74HC595.11 (SCK), EXTOUT1.5, JP1.5
D7: 74HC595.12 (RCK), EXTOUT1.3, JP1.1
GND: 74HC595.8 (GND), BAT1.P$1 (-), C1.-, C2.-, C3.2, C4.2, C5.2, D2.A, D3.A, DS1307.4 (GND), EXTOUT1.2, EXTOUT1.4, EXTOUT1.6, J0.1, JP1.4, JP2.1, JP3.1, JP4.1, JP7.1, JP7.2, JP7.3, JP7.4, JP7.5, LM2596S-5.0.3 (GND), LM2596S-5.0.5 (!ON!/OFF), LM2596S-5.0.6 (HS), PCF8591.5 (A0), PCF8591.6 (A1), PCF8591.7 (A2), PCF8591.8 (VSS), PCF8591.12 (EXT), PCF8591.13 (AGND), RLED.2, T1.1 (M1), T2.1 (M1), T3.1 (M1), T4.1 (M1), T5.1 (M1), T6.1 (M1), T7.1 (M1), T8.1 (M1), TP2.1
unnamed: PWR_LED.C, RLED.1
unnamed: C1.+, D1.C, LM2596S-5.0.1 (VIN)
unnamed: RN2.1, T1.3 (G)
unnamed: 74HC595.5 (QF), RN3.7 (2)
unnamed: 74HC595.6 (QG), RN3.6 (2)
unnamed: J0.2, J2.2, TP1.1
unnamed: 74HC595.7 (QH), RN3.5 (2)
unnamed: D2.C, L1.1, LM2596S-5.0.2 (OUT)
unnamed: DS1307.1 (X1), X1.1
unnamed: 74HC595.4 (QE), RN3.8 (2)
unnamed: 74HC595.3 (QD), RN2.5 (2)
unnamed: 74HC595.2 (QC), RN2.6 (2)
unnamed: 74HC595.1 (QB), RN2.7 (2)
unnamed: 74HC595.15 (QA), RN2.8 (2)
unnamed: RN2.2 (1), T2.3 (G)
unnamed: S12.1, T1.4 (M2)
unnamed: S12.2, T2.4 (M2)
unnamed: S34.1, T3.4 (M2)
unnamed: RN2.3 (1), T3.3 (G)
unnamed: S34.2, T4.4 (M2)
unnamed: RN2.4 (1), T4.3 (G)
unnamed: S56.1, T5.4 (M2)
unnamed: S56.2, T6.4 (M2)
unnamed: S78.1, T7.4 (M2)
unnamed: S78.2, T8.4 (M2)
unnamed: RN3.1, T5.3 (G)
unnamed: RN3.2 (1), T6.3 (G)
unnamed: RN3.3 (1), T7.3 (G)
unnamed: RN3.4 (1), T8.3 (G)
unnamed: DS1307.2 (X2), X1.4 (2)
unnamed: BAT1.P$2 (+), DS1307.3 (VBAT)
QH*: 74HC595.9 (QH*), EXTOUT1.7
SCL: DS1307.6 (SCL), JP1.6, JP3.2, JP4.2, PCF8591.10 (SCL)
SDA: DS1307.5 (SDA), JP1.7, JP3.3, JP4.3, PCF8591.9 (SDA)
VCC: 74HC595.10 (SCL), 74HC595.16 (VCC), C3.1, C5.1, EXTOUT1.8, JP1.8, JP4.4, JP6.1, JP6.2, JP6.3, JP6.4, JP6.5, PCF8591.14 (VREF), PCF8591.16 (VDD), ROE.2
VIN: C4.1, D3.C, DS1307.8 (VCC), F2.2, JP2.2, JP2.3, JP3.4, PWR_LED.A, TP3.1
VIN_PRE: C2.+, F2.1, L1.2, LM2596S-5.0.4 (FB)

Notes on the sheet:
Power Supply
Valve Driver
Data
Clock
Latch
330x4 Isolated ResNet
Ext. Board Portion
!OE
RTC
